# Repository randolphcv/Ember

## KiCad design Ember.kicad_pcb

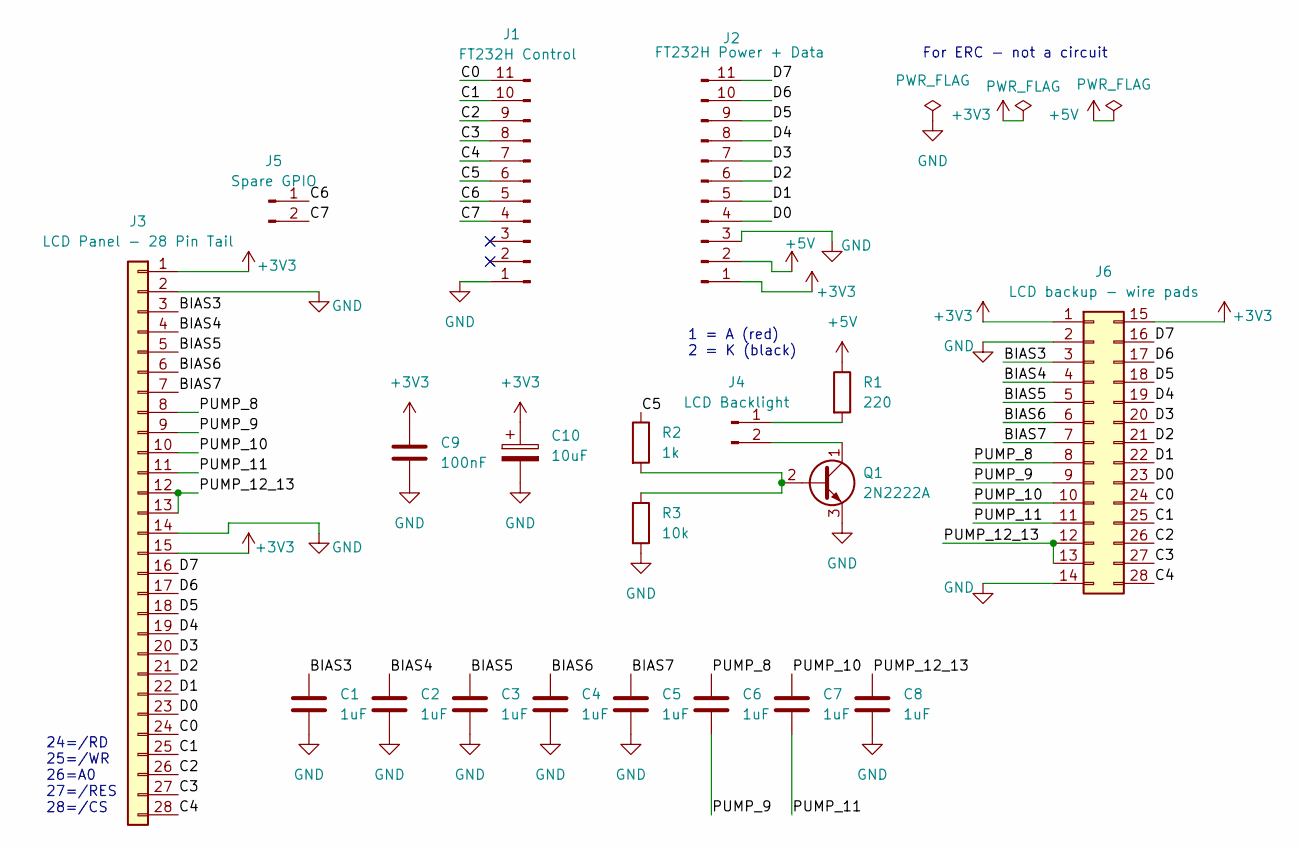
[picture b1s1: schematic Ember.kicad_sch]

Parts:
C1, C2, C3, C4, C5, C6, C7, C8: 1uF; C_Disc_D4.7mm_W2.5mm_P5.00mm
C9: 100nF; C_Disc_D4.7mm_W2.5mm_P5.00mm
C10: 10uF; CP_Radial_D5.0mm_P2.50mm
J1: FT232H Control; PinSocket_1x11_P2.54mm_Vertical
J2: FT232H Power + Data; PinSocket_1x11_P2.54mm_Vertical
J3: LCD Panel - 28 Pin Tail; Hirose_FH12-28S-0.5SH_1x28-1MP_P0.50mm_Horizontal
J4: LCD Backlight; PinSocket_1x02_P2.54mm_Horizontal
J5: Spare GPIO; PinHeader_1x02_P2.54mm_Vertical
J6: LCD backup - wire pads; PinHeader_2x14_P2.54mm_Vertical
Q1: 2N2222A; TO-92_Inline
R1: 220; R_Axial_DIN0207_L6.3mm_D2.5mm_P10.16mm_Horizontal
R2: 1k; R_Axial_DIN0207_L6.3mm_D2.5mm_P10.16mm_Horizontal
R3: 10k; R_Axial_DIN0207_L6.3mm_D2.5mm_P10.16mm_Horizontal

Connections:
+3V3: C9.1, C10.1, J2.1, J3.1, J3.15, J6.1, J6.15
+5V: J2.2, R1.1
/BIAS3: C1.1, J3.3, J6.3
/BIAS4: C2.1, J3.4, J6.4
/BIAS5: C3.1, J3.5, J6.5
/BIAS6: C4.1, J3.6, J6.6
/BIAS7: C5.1, J3.7, J6.7
/C0: J1.11 (Pin_22), J3.24, J6.24
/C1: J1.10 (Pin_21), J3.25, J6.25
/C2: J1.9 (Pin_20), J3.26, J6.26
/C3: J1.8 (Pin_19), J3.27, J6.27
/C4: J1.7 (Pin_18), J3.28, J6.28
/C5: J1.6 (Pin_17), R2.1
/C6: J1.5 (Pin_16), J5.1
/C7: J1.4 (Pin_15), J5.2
/D0: J2.4, J3.23, J6.23
/D1: J2.5, J3.22, J6.22
/D2: J2.6, J3.21, J6.21
/D3: J2.7, J3.20, J6.20
/D4: J2.8, J3.19, J6.19
/D5: J2.9, J3.18, J6.18
/D6: J2.10, J3.17, J6.17
/D7: J2.11, J3.16, J6.16
/PUMP_8: C6.1, J3.8, J6.8
/PUMP_9: C6.2, J3.9, J6.9
/PUMP_10: C7.1, J3.10, J6.10
/PUMP_11: C7.2, J3.11, J6.11
/PUMP_12_13: C8.1, J3.12, J3.13, J6.12, J6.13
GND: C1.2, C2.2, C3.2, C4.2, C5.2, C8.2, C9.2, C10.2, J1.1 (Pin_12), J2.3, J3.2, J3.14, J6.2, J6.14, Q1.3 (E), R3.2
unnamed: J4.1, R1.2
unnamed: J4.2, Q1.1 (C)
unnamed: Q1.2 (B), R2.2, R3.1

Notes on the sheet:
24=/RD 25=/WR 26=A0 27=/RES 28=/CS
For ERC - not a circuit
1 = A (red) 2 = K (black)

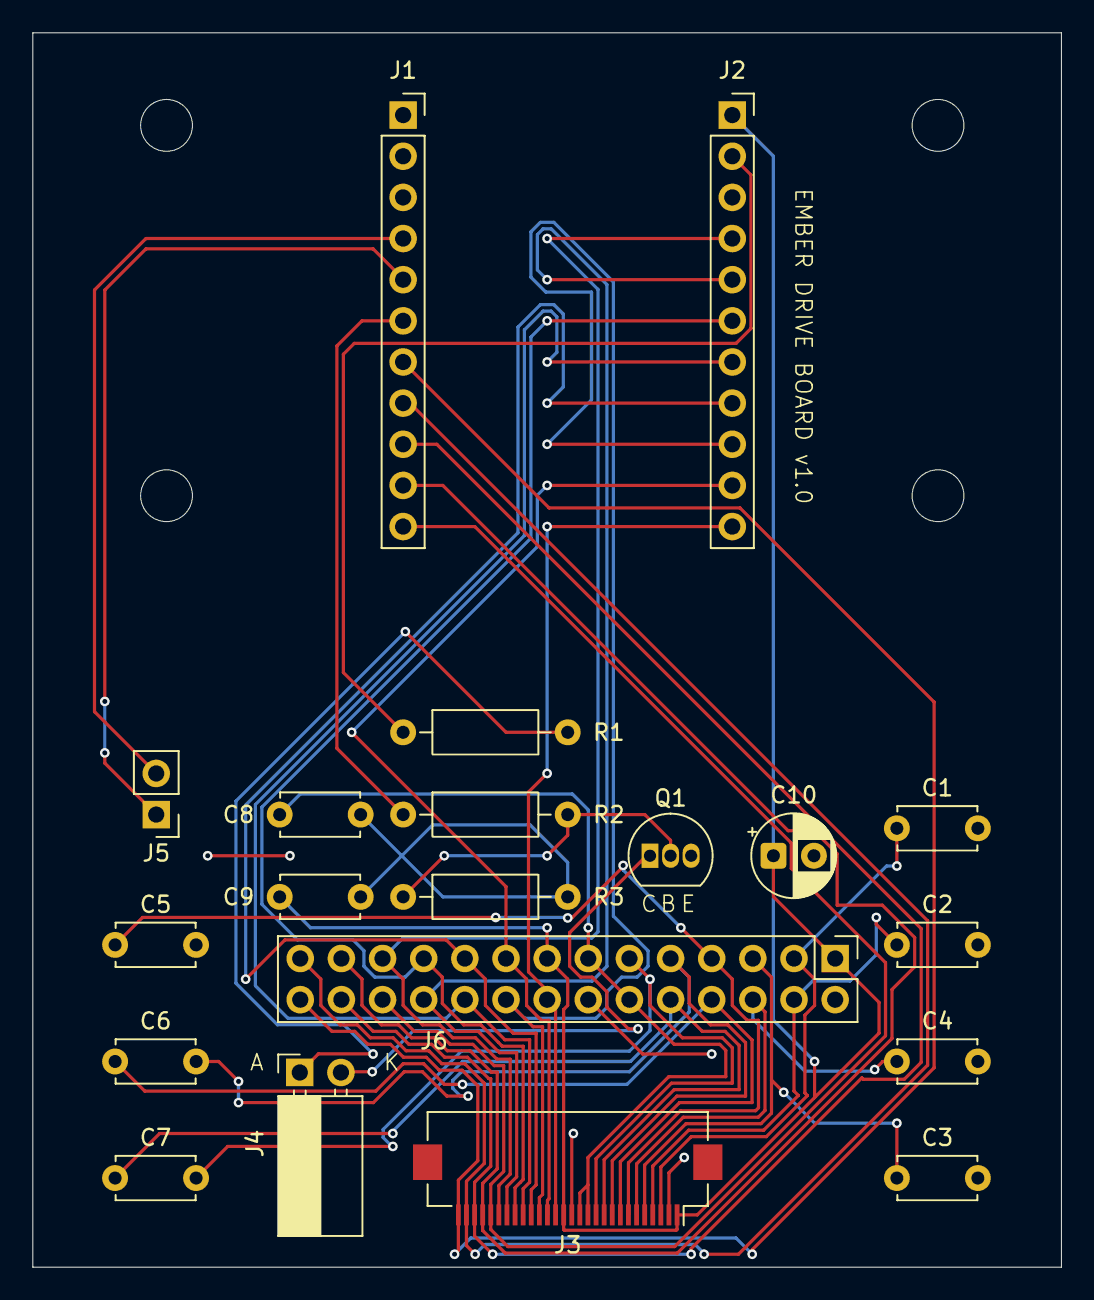
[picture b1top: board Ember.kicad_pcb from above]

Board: 2 copper layers, 63.5 x 76.2 mm, 20 parts (0 on the bottom side), 32 nets.
